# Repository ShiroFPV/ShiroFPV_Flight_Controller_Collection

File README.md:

# ShiroFPV Flight Controller Collection

Open-source FPV flight controller hardware — schematic, PCB layout, symbols and
firmware target, all published in full.

Designed in KiCad, targeted at Betaflight, and licensed so it stays open.

More at **[shirofpv.com/flight-controller](https://shirofpv.com/flight-controller)**

## Boards

| Board | Size | MCU | Analog OSD | Status |
|---|---|---|---|---|
| [**V1** `SFVPF435`](V1_30x30_SFVPF435/) | 30.5 × 30.5 | AT32F435RGT7 | ✅ AT7456 | Released |
| [**V2** `SFVPF435`](V2_20x20_SFVPF435/) | 20.5 × 20.5 | AT32F435CGT7 (48-pin) | ❌ digital only | Released |

---

## V1 — `SFVPF435` (30.5 × 30.5)

| | |
|---|---|
| **MCU** | Artery AT32F435RGT7, up to 288 MHz |
| **Gyro** | ICM-20602 |
| **Baro** | BME280 |
| **OSD** | AT7456 |
| **Blackbox** | 16 Mb onboard flash |
| **USB** | USB-C |
| **Mount** | 30.5 × 30.5 mm standard stack |
| **Firmware** | Betaflight |

### Layout

```
V1_30x30_SFVPF435/
├─ Shematic/          hardware sources — CERN-OHL-S v2
│  ├─ ShiroFPV_Flight_Controller.kicad_sch    schematic
│  ├─ ShiroFPV_Flight_Controller.kicad_pcb    PCB layout
│  ├─ All_Own_Symbols.kicad_sym               custom symbols
│  ├─ All_Own_Symbols.pretty/                 custom footprints
│  └─ .glb                                    3D model
└─ Release/           firmware — GPL-3.0-or-later
   ├─ config.h                                Betaflight target config
   └─ SFPVF435V1.hex                          compiled firmware
```

> Note: `Shematic/` is a typo for `Schematic/` kept as-is so existing links and
> clones don't break.

---

## V2 — `SFVPF435` (20 × 20)

A compact, modern 20.5 × 20.5 mm flight controller designed specifically for lightweight HD-FPV freestyle and racing builds.

| | |
|---|---|
| **MCU** | Artery AT32F435CGT7 (LQFP-48), up to 288 MHz |
| **Gyro** | ICM-42605 (SPI1, 8 kHz sampling) |
| **Baro** | SPL07-003 (I2C1, address `0x76`) |
| **Analog OSD** | **None** — digital video only (HD Zero, DJI O3/O4, Walksnail) |
| **Motors** | 4x DShot motor pads (M1–M4) on TMR5/TMR3 with Bidirectional DShot (RPM filtering) |
| **UARTs** | 5x hardware UARTs (Receiver default on UART5, VTX on UART4) |
| **I2C** | Free I2C1 bus exposed for external compass |
| **USB** | USB-C |
| **Mount** | 20.5 × 20.5 mm M3 / M2 with grommets |
| **Firmware** | Betaflight |

Dropping the legacy analog OSD chip (AT7456E) saves board space, weight, and eliminates video noise on modern digital setups.

### Layout

```
V2_20x20_SFVPF435/
├─ Shematic/          hardware sources — CERN-OHL-S v2
│  ├─ ShiroFPV_Flight_Controller.kicad_sch    schematic
│  ├─ ShiroFPV_Flight_Controller.kicad_pcb    PCB layout
│  ├─ All_Own_Symbols.kicad_sym               custom symbols
│  ├─ All_Own_Symbols.pretty/                 custom footprints
│  └─ .glb                                    3D model
└─ Release/           firmware — GPL-3.0-or-later
   ├─ config.h                                Betaflight target config
   └─ SFPVF435V2.hex                          compiled firmware
```

Details in [`V2_20x20_SFVPF435/`](V2_20x20_SFVPF435/).

---

## Datasheets

Artery's documentation is not redistributed here — it is their copyright.
Download it from the source:

- **AT32F435** — [product page](https://www.arterychip.com/en/product/AT32F435.jsp)
  (datasheet + reference manual)
- **AT32F437** — [product page](https://www.arterychip.com/en/product/AT32F437.jsp)

---

## Building one

The design files are complete — schematic, layout, custom symbols and
footprints. Open `ShiroFPV_Flight_Controller.kicad_pro` in KiCad 8 or newer,
export gerbers, and send them to whichever fab you like.

Flash `SFPVF435V1.hex` or `SFPVF435V2.hex` with the Betaflight Configurator, or build from the
Betaflight sources using `config.h` as the target definition.

It flies. Mostly.

---

## Licence

Two licences, because there are two kinds of work here. Both copyleft.

| Part | Licence |
|---|---|
| Hardware design (`Shematic/`) | [CERN-OHL-S v2](LICENSE) |
| Firmware (`Release/`) | [GPL-3.0-or-later](V1_30x30_SFVPF435/Release/LICENSE) |

**Short version:** use it, modify it, build it, sell it. If you distribute a
modified version, publish your sources under the same licence. You can profit
from this design — you just can't close it.

Full detail and reasoning in **[LICENSING.md](LICENSING.md)**.

---

## Contributing

Issues and pull requests welcome — improvements, fixes, or a revision of your
own. Contributions are accepted under the same licences as above.

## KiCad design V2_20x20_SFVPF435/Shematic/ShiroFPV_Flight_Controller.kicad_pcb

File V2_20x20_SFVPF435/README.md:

# V2 — `SFVPF435` 20 × 20

A compact, high-performance 20.5 × 20.5 mm flight controller powered by the **Artery AT32F435CGT7** (ARM Cortex-M4F @ 288 MHz), designed specifically for lightweight HD-FPV freestyle and racing drones.

## Specifications

| | |
|---|---|
| **MCU** | Artery AT32F435CGT7 (LQFP-48), up to 288 MHz |
| **Gyro** | ICM-42605 via SPI1 (low-noise, up to 8 kHz sampling) |
| **Baro** | SPL07-003 via I2C1 (high-precision altitude sensor) |
| **Analog OSD** | **None** — digital video only (HDZero, Walksnail, DJI O3/O4) |
| **Motors** | 4x DShot motor pads (`PB12`, `PB13`, `PB0`, `PB1`) with Bidirectional DShot (RPM filtering) |
| **UARTs** | 5x hardware UARTs (`UART1`, `UART2`, `UART3`, `UART4`, `UART5` default for CRSF/ELRS) |
| **I2C** | Dedicated I2C1 bus for external compass |
| **Audio/Beeper** | Onboard active-high buzzer driver (N-MOSFET on `PC13`) |
| **LEDs** | Blue (`PB14`) / Green (`PB15`) |
| **ADC** | VBAT (`PA0`, scale 110) & Current sense (`PA1`) |
| **Mount** | 20.5 × 20.5 mm (M3 / M2 with grommets) |
| **Firmware** | Betaflight |

Dropping the legacy analog OSD chip (AT7456E) saves substantial board space and eliminates video noise on modern digital FPV setups.

## Layout

```
V2_20x20_SFVPF435/
├─ Shematic/                                  hardware sources — CERN-OHL-S v2
│  ├─ ShiroFPV_Flight_Controller.kicad_sch    schematic
│  ├─ ShiroFPV_Flight_Controller.kicad_pcb    PCB layout
│  ├─ All_Own_Symbols.kicad_sym               custom symbols
│  ├─ All_Own_Symbols.pretty/                 custom footprints & 3D models
│  └─ .glb                                    3D model
└─ Release/                                   firmware — GPL-3.0-or-later
   ├─ config.h                                Betaflight target config
   └─ SFPVF435V2.hex                          compiled firmware
```

Same two-licence split as V1 — see [LICENSING.md](../LICENSING.md).

## Flashing Betaflight

1. Connect the flight controller via USB.
2. In Betaflight Configurator, open the **Firmware Flasher** tab.
3. Click **Load Firmware [Local]** and select `Release/SFPVF435V2.hex`.
4. Enable **Full chip erase** and click **Flash Firmware**.

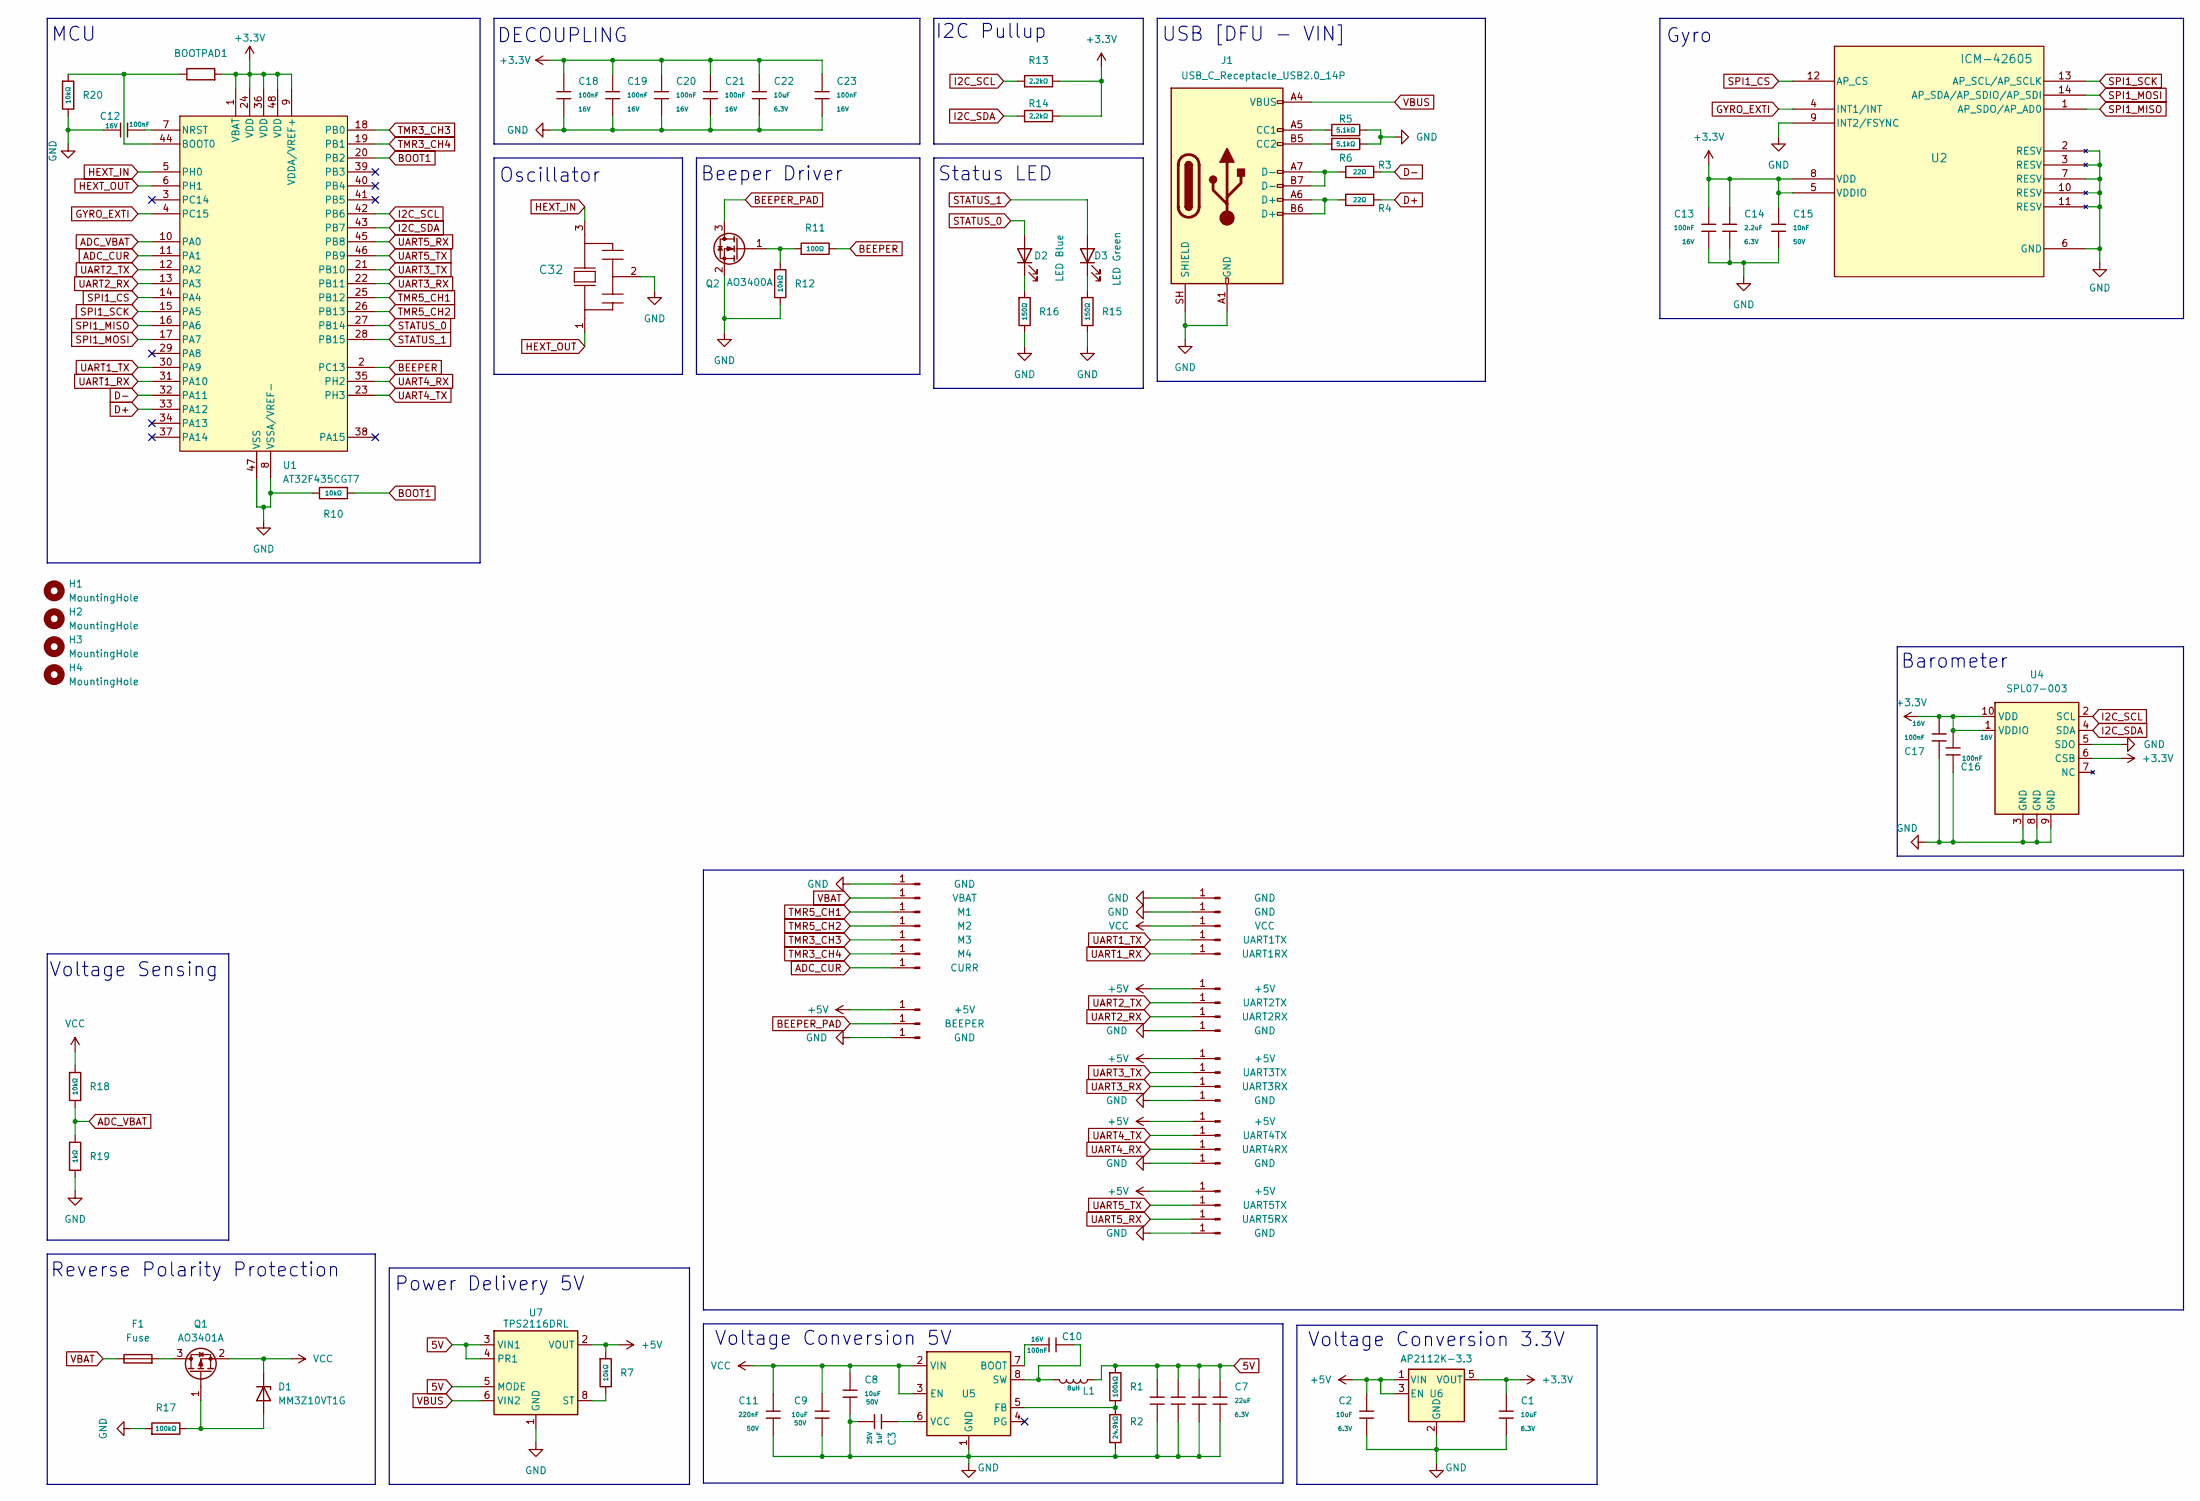
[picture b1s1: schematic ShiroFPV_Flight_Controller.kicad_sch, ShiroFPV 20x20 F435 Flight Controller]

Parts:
BOOTPAD1: SolderJumper-2_P1.3mm_Open_Pad1.0x1.5mm
C1, C2, C22: 10uF; C_0402; Voltage Rated 6.3V; Tolerance ±20%; Part CL05A106MQ5NUNC; LCSC C15525
C3: 1uF; C_0402; Voltage Rated 25V; Tolerance ±10%; Part CL05A105KA5NQNC; LCSC C52923
C4, C5, C6, C7: 22uF; C_0603; Voltage Rated 6.3V; Tolerance ±20%; Part CL10A226MQ8NRNC; LCSC C59461
C8, C9: 10uF; C_0805; Voltage Rated 50V; Tolerance ±10%; Part GRM21BR61H106KE43L; LCSC C440198
C10, C12, C13, C16, C17, C18, C19, C20, C21, C23: 100nF; C_0402; Voltage Rated 16V; Tolerance ±10%; Part CL05B104KO5NNNC; LCSC C1525
C11: 220nF; C_0805; Voltage Rated 50V; Tolerance ±10%; Part CL21B224KBFNNNE; LCSC C5378
C14: 2.2uF; C_0402; Voltage Rated 6.3V; Tolerance ±20%; Part CL05A225MQ5NSNC; LCSC C12530
C15: 10nF; C_0402; Voltage Rated 50V; Tolerance ±10%; Part CL05B103KB5NNNC; LCSC C15195
C32: CSTCE8M00G52-R0; Resonator_SMD_Murata_CSTxExxV-3Pin_3.0x1.1mm; MPN CSTNE8M00G520000R0
D1: MM3Z10VT1G; D_SOD-323_HandSoldering; MPN LM3Z10VT1G
D2: LED Blue; LED_0603_1608Metric
D3: LED Green; LED_0603_1608Metric
F1: Fuse; Fuse_1206_3216Metric
H1, H2, H3, H4: MountingHole; MountingHole_3.2mm_M3
J1: USB_C_Receptacle_USB2.0_14P; USB_C_Receptacle_HRO_TYPE-C-31-M-12
J2, J3, J12, J27, J29, J31, J36, J40: GND; TestPoint_Pad_1.0x1.0mm
J13: VCC; TestPoint_Pad_1.0x1.0mm
J14: UART1TX; TestPoint_Pad_1.0x1.0mm
J15: UART1RX; TestPoint_Pad_1.0x1.0mm
J16: UART2TX; TestPoint_Pad_1.0x1.0mm
J17: UART2RX; TestPoint_Pad_1.0x1.0mm
J18: UART3TX; TestPoint_Pad_1.0x1.0mm
J19: UART3RX; TestPoint_Pad_1.0x1.0mm
J20: UART4TX; TestPoint_Pad_1.0x1.0mm
J21: UART4RX; TestPoint_Pad_1.0x1.0mm
J22: M1; TestPoint_Pad_1.0x1.0mm
J23: M2; TestPoint_Pad_1.0x1.0mm
J24: M3; TestPoint_Pad_1.0x1.0mm
J25: M4; TestPoint_Pad_1.0x1.0mm
J26: CURR; TestPoint_Pad_1.0x1.0mm
J28, J30, J32, J33, J39: +5V; TestPoint_Pad_1.0x1.0mm
J34: UART5TX; TestPoint_Pad_1.0x1.0mm
J35: UART5RX; TestPoint_Pad_1.0x1.0mm
J37: VBAT; TestPoint_Pad_1.0x1.0mm
J38: BEEPER; TestPoint_Pad_1.0x1.0mm
L1: 8uH; L_Wuerth_MAPI-4030
Q1: AO3401A; SOT-23
Q2: AO3400A; SOT-23
R1, R17: 100kΩ; R_0402; Overload Voltage (Max) 50V; Tolerance ±1%; Part 0402WGF1003TCE; LCSC C25741
R2: 24.9kΩ; R_0402
R3, R4: 22Ω; R_0402; Overload Voltage (Max) 50V; Tolerance ±1%; Part 0402WGF220JTCE; LCSC C25092
R5, R6: 5.1kΩ; R_0402; Overload Voltage (Max) 50V; Tolerance ±1%; Part 0402WGF5101TCE; LCSC C25905
R7, R10, R12, R18, R20: 10kΩ; R_0402; Overload Voltage (Max) 50V; Tolerance ±1%; Part 0402WGF1002TCE; LCSC C25744
R11: 100Ω; R_0402; Overload Voltage (Max) 50V; Tolerance ±1%; Part 0402WGF1000TCE; LCSC C25076
R13, R14: 2.2kΩ; R_0402; Overload Voltage (Max) 50V; Tolerance ±1%; Part 0402WGF2201TCE; LCSC C25879
R15, R16: 150Ω; R_0402; Overload Voltage (Max) 50V; Tolerance ±1%; Part 0402WGF1500TCE; LCSC C25082
R19: 1kΩ; R_0402; Overload Voltage (Max) 50V; Tolerance ±1%; Part 0402WGF1001TCE; LCSC C11702
U1: AT32F435CGT7; LQFP-48_7x7mm_P0.5mm; MPN AT32F435CGT7
U2: ICM-42605; LGA-14_3x2.5mm_P0.5mm_LayoutBorder3x4y
U4: SPL07-003; LGA-10_L2.0-W2.0-P0.50-BL; LCSC C3253727
U5: LMR33630ADDA; Texas_HSOP-8-1EP_3.9x4.9mm_P1.27mm_ThermalVias
U6: AP2112K-3.3; SOT-23-5
U7: TPS2116DRL; SOT-583-8

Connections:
5V: C4.1, C5.1, C6.1, C7.1, L1.1, R1.1, U7.3 (VIN1), U7.4 (PR1), U7.5 (MODE)
+3.3V: BOOTPAD1.2, C1.1, C13.1, C14.1, C15.1, C16.2, C17.1, C18.1, C19.1, C20.1, C21.1, C22.1, C23.1, R13.2, R14.2, U1.1 (VBAT), U1.9 (VDDA/VREF+), U1.24 (VDD), U1.36 (VDD), U1.48 (VDD), U2.5 (VDDIO), U2.8 (VDD), U4.1 (VDDIO), U4.6 (CSB), U4.10 (VDD), U6.5 (VOUT)
+5V: C2.1, J28.1 (Pin_1_1), J30.1 (Pin_1_1), J32.1 (Pin_1_1), J33.1 (Pin_1_1), J39.1 (Pin_1_1), R7.1, U6.1 (VIN), U6.3 (EN), U7.2 (VOUT), U7.7 (VOUT)
ADC_CUR: J26.1 (Pin_1_1), U1.11 (PA1)
ADC_VBAT: R18.2, R19.1, U1.10 (PA0)
BEEPER: R11.2, U1.2 (PC13)
BEEPER_PAD: J38.1 (Pin_1_1), Q2.3 (D)
BOOT1: R10.1, U1.20 (PB2)
D+: R4.1, U1.33 (PA12)
D-: R3.2, U1.32 (PA11)
GND: C1.2, C2.2, C3.2, C4.2, C5.2, C6.2, C7.2, C8.2, C9.2, C11.2, C12.2, C13.2, C14.2, C15.2, C16.1, C17.2, C18.2, C19.2, C20.2, C21.2, C22.2, C23.2, C32.2, J1.A1 (GND), J1.A12 (GND), J1.B1 (GND), J1.B12 (GND), J1.SH (SHIELD), J2.1 (Pin_1_1), J3.1 (Pin_1_1), J12.1 (Pin_1_1), J27.1 (Pin_1_1), J29.1 (Pin_1_1), J31.1 (Pin_1_1), J36.1 (Pin_1_1), J40.1 (Pin_1_1), Q2.2 (S), R2.2, R5.2, R6.2, R10.2, R12.2, R15.2, R16.2, R17.1, R19.2, R20.2, U1.8 (VSSA/VREF-), U1.47 (VSS), U2.2 (RESV), U2.3 (RESV), U2.6 (GND), U2.7 (RESV), U2.9 (INT2/FSYNC), U2.10 (RESV), U2.11 (RESV), U4.3 (GND), U4.5 (SDO), U4.8 (GND), U4.9 (GND), U5.1 (GND), U5.9 (GND), U6.2 (GND), U7.1 (GND)
GYRO_EXTI: U1.4 (PC15), U2.4 (INT1/INT)
HEXT_IN: C32.3, U1.5 (PH0)
HEXT_OUT: C32.1, U1.6 (PH1)
I2C_SCL: R13.1, U1.42 (PB6), U4.2 (SCL)
I2C_SDA: R14.1, U1.43 (PB7), U4.4 (SDA)
unnamed: D1.2 (A), Q1.1 (G), R17.2
unnamed: D2.1 (K), R16.1
unnamed: D3.1 (K), R15.1
unnamed: J1.A5 (CC1), R5.1
unnamed: J1.B5 (CC2), R6.1
unnamed: J1.A6 (D+), J1.B6 (D+), R4.2
unnamed: J1.A7 (D-), J1.B7 (D-), R3.1
unnamed: F1.2, Q1.3 (D)
unnamed: Q2.1 (G), R11.1, R12.1
unnamed: BOOTPAD1.1, R20.1, U1.44 (BOOT0)
unnamed: C12.1, U1.7 (NRST)
unnamed: C10.1, U5.7 (BOOT)
unnamed: R1.2, R2.1, U5.5 (FB)
unnamed: C10.2, L1.2, U5.8 (SW)
unnamed: C3.1, U5.6 (VCC)
unnamed: R7.2, U7.8 (ST)
SPI1_CS: U1.14 (PA4), U2.12 (AP_CS)
SPI1_MISO: U1.16 (PA6), U2.1 (AP_SDO/AP_AD0)
SPI1_MOSI: U1.17 (PA7), U2.14 (AP_SDA/AP_SDIO/AP_SDI)
SPI1_SCK: U1.15 (PA5), U2.13 (AP_SCL/AP_SCLK)
STATUS_0: D2.2 (A), U1.27 (PB14)
STATUS_1: D3.2 (A), U1.28 (PB15)
TMR3_CH3: J24.1 (Pin_1_1), U1.18 (PB0)
TMR3_CH4: J25.1 (Pin_1_1), U1.19 (PB1)
TMR5_CH1: J22.1 (Pin_1_1), U1.25 (PB12)
TMR5_CH2: J23.1 (Pin_1_1), U1.26 (PB13)
UART1_RX: J15.1 (Pin_1_1), U1.31 (PA10)
UART1_TX: J14.1 (Pin_1_1), U1.30 (PA9)
UART2_RX: J17.1 (Pin_1_1), U1.13 (PA3)
UART2_TX: J16.1 (Pin_1_1), U1.12 (PA2)
UART3_RX: J19.1 (Pin_1_1), U1.22 (PB11)
UART3_TX: J18.1 (Pin_1_1), U1.21 (PB10)
UART4_RX: J21.1 (Pin_1_1), U1.35 (PH2)
UART4_TX: J20.1 (Pin_1_1), U1.23 (PH3)
UART5_RX: J35.1 (Pin_1_1), U1.45 (PB8)
UART5_TX: J34.1 (Pin_1_1), U1.46 (PB9)
VBAT: F1.1, J37.1 (Pin_1_1)
VBUS: J1.A4 (VBUS), J1.A9 (VBUS), J1.B4 (VBUS), J1.B9 (VBUS), U7.6 (VIN2)
VCC: C8.1, C9.1, C11.1, D1.1 (K), J13.1 (Pin_1_1), Q1.2 (S), R18.1, U5.2 (VIN), U5.3 (EN)

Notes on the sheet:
Voltage Sensing
USB [DFU - VIN]
Status LED
DECOUPLING
Barometer
I2C Pullup
Voltage Conversion 5V
Oscillator
Power Delivery 5V
Beeper Driver
MCU
Reverse Polarity Protection
Gyro
Voltage Conversion 3.3V

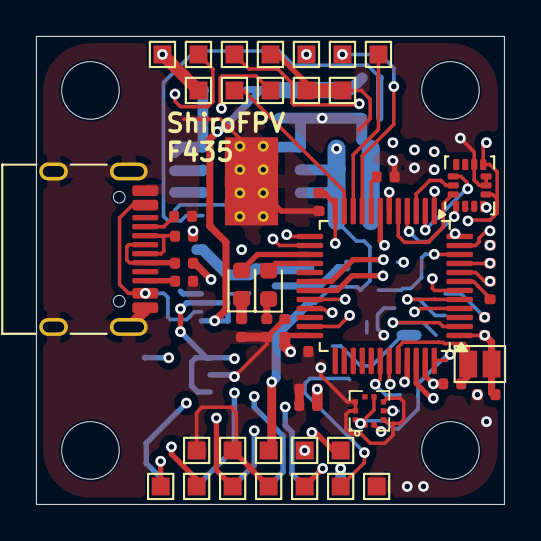
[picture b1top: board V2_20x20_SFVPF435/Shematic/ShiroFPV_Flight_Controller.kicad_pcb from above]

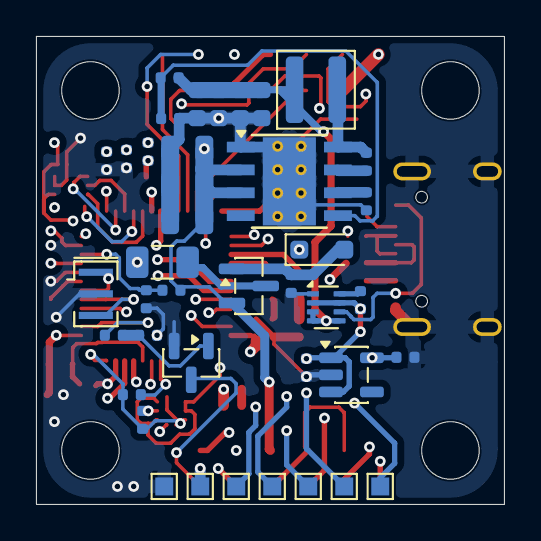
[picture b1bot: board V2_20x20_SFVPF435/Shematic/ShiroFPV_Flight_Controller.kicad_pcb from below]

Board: 4 copper layers, 26.0 x 26.0 mm, 92 parts (40 on the bottom side), 55 nets.

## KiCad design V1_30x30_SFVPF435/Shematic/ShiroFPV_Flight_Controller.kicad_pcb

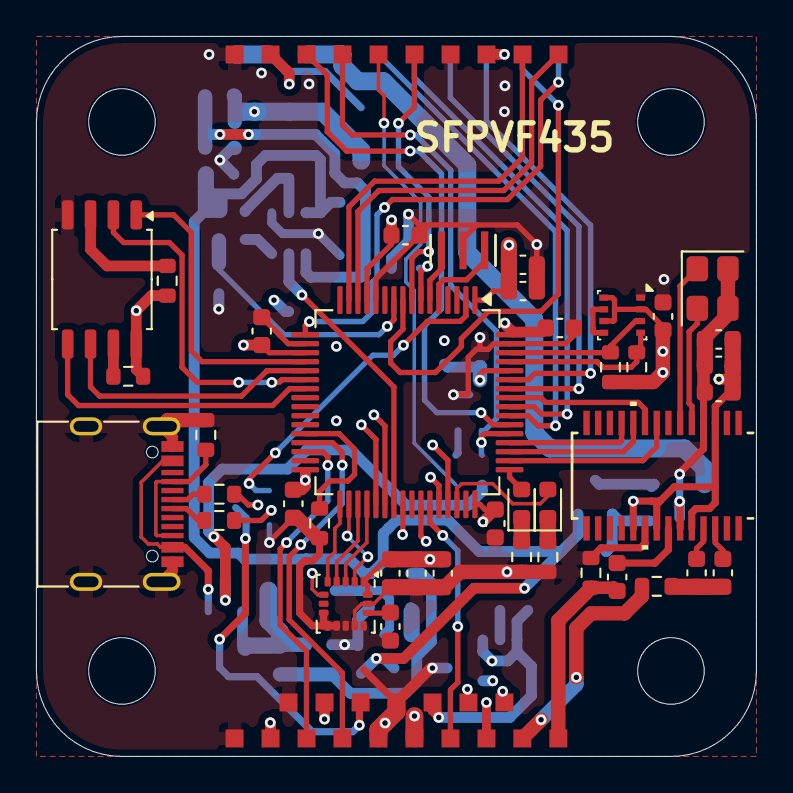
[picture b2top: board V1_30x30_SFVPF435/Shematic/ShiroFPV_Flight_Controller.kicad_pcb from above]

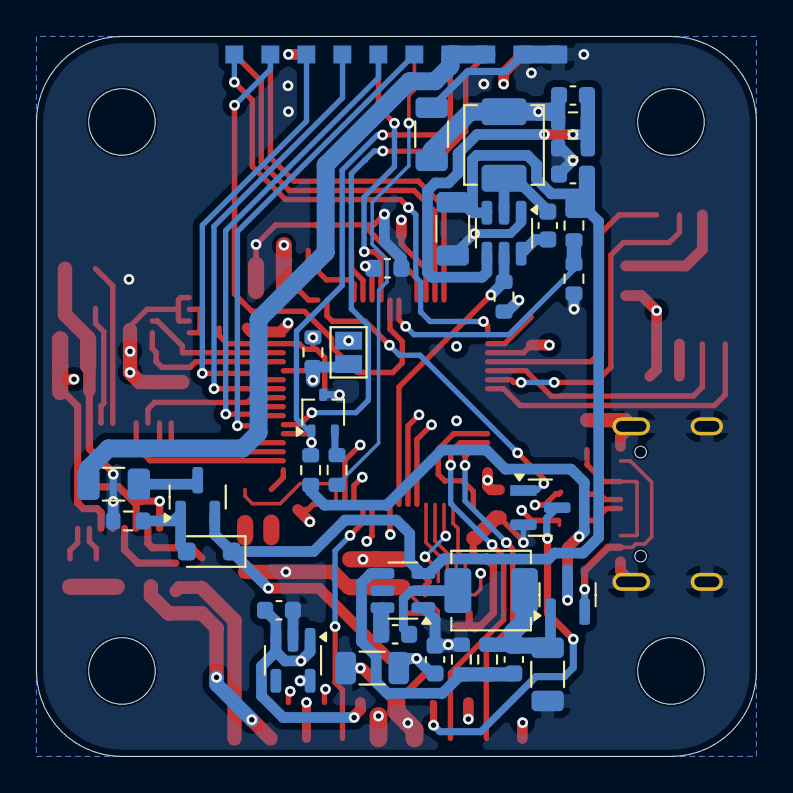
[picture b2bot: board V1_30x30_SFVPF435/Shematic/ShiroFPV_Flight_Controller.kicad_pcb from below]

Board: 4 copper layers, 40.0 x 40.0 mm, 112 parts (45 on the bottom side), 79 nets.

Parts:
C1, C2, C4, C6, C7, C10, C11, C12, C13, C15, C16, C20, C23, C25, C26, C27, C28, C29: 100nF; C_0603_1608Metric
C3: 10nF; C_0603_1608Metric
C5, C31: 1uF; C_0603_1608Metric
C8, C9: 47uF; C_0603_1608Metric
C14, C38: 10uF; C_1206_3216Metric
C17: 100pF; C_0603_1608Metric
C18, C19: 47uF; C_1206_3216Metric
C22: 150pF; C_0603_1608Metric
C32: CSTCE8M00G52-R0; 8MHz-Osciallator.kicad_sym
C39: 2.2uF; C_0603_1608Metric
D1: MM3Z10VT1G; D_SOD-323_HandSoldering
D2: LED Blue; LED_0603_1608Metric
D3: LED Yellow; LED_0603_1608Metric
D4: PMEG4005CT,215; SOT-23
F1: Fuse; Fuse_1206_3216Metric
J1, J2, J46: GND; TestPoint_Pad_1.0x1.0mm_No_Silkscreen
J3, J4: VBAT; TestPoint_Pad_1.0x1.0mm_No_Silkscreen
J5: M1; TestPoint_Pad_1.0x1.0mm_No_Silkscreen
J6: M2; TestPoint_Pad_1.0x1.0mm_No_Silkscreen
J7: M3; TestPoint_Pad_1.0x1.0mm_No_Silkscreen
J8: M4; TestPoint_Pad_1.0x1.0mm_No_Silkscreen
J9: CUR; TestPoint_Pad_1.0x1.0mm_No_Silkscreen
J10: TLM; TestPoint_Pad_1.0x1.0mm_No_Silkscreen
J11: Video_Out; TestPoint_Pad_1.0x1.0mm_No_Silkscreen
J12: Video_IN; TestPoint_Pad_1.0x1.0mm_No_Silkscreen
J13: 5V3; TestPoint_Pad_1.0x1.0mm_No_Silkscreen
J14: RX3; TestPoint_Pad_1.0x1.0mm_No_Silkscreen
J15: TX3; TestPoint_Pad_1.0x1.0mm_No_Silkscreen
J16: GND3; TestPoint_Pad_1.0x1.0mm_No_Silkscreen
J17: 5V4; TestPoint_Pad_1.0x1.0mm_No_Silkscreen
J18: RX4; TestPoint_Pad_1.0x1.0mm_No_Silkscreen
J19: TX4; TestPoint_Pad_1.0x1.0mm_No_Silkscreen
J20: GND4; TestPoint_Pad_1.0x1.0mm_No_Silkscreen
J24: +5V; TestPoint_Pad_1.0x1.0mm_No_Silkscreen
J25: RSSI; TestPoint_Pad_1.0x1.0mm_No_Silkscreen
J26: GND5; TestPoint_Pad_1.0x1.0mm_No_Silkscreen
J29: SBUS; TestPoint_Pad_1.0x1.0mm_No_Silkscreen
J30: 5V5; TestPoint_Pad_1.0x1.0mm_No_Silkscreen
J31: RX5; TestPoint_Pad_1.0x1.0mm_No_Silkscreen
J32: TX5; TestPoint_Pad_1.0x1.0mm_No_Silkscreen
J33: RX6; TestPoint_Pad_1.0x1.0mm_No_Silkscreen
J34: 5V6; TestPoint_Pad_1.0x1.0mm_No_Silkscreen
J35: GND6; TestPoint_Pad_1.0x1.0mm_No_Silkscreen
J36: TX6; TestPoint_Pad_1.0x1.0mm_No_Silkscreen
J37: 10V; TestPoint_Pad_1.0x1.0mm_No_Silkscreen
J38: RX1; TestPoint_Pad_1.0x1.0mm_No_Silkscreen
J39: TX1; TestPoint_Pad_1.0x1.0mm_No_Silkscreen
J40: GND1; TestPoint_Pad_1.0x1.0mm_No_Silkscreen
J42: B-; TestPoint_Pad_1.0x1.0mm_No_Silkscreen
JP1: SolderJumper_2_Open; SolderJumper-2_P1.3mm_Open_Pad1.0x1.5mm
L1: 10uH; L_APV_APH0412
L2: 15uH; L_APV_APH0412
P1: USB_C_Plug_USB2.0; USB_C_Receptacle_G-Switch_GT-USB-7010ASV
Q1: AO3401A; SOT-23
Q2: AO3400A; SOT-23
Q3: BC817W; SOT-323_SC-70
R1, R7, R11: 100K; R_0603_1608Metric
R2: 12.3K; R_0603_1608Metric
R3, R4: 75R; R_0603_1608Metric
R5, R6, R9, R10, R19, R20: 10K; R_0603_1608Metric
R8: 6.2K; R_0603_1608Metric
R12, R13: 22R; R_0603_1608Metric
R14: 5.1K; R_0603_1608Metric
R15, R16: 150R; R_0603_1608Metric
R17, R29: 2.2K; R_0603_1608Metric
R21: 2K; R_0603_1608Metric
R22: 4.7K; R_0603_1608Metric
R27: 18K; R_0603_1608Metric
U1: AT32F435RGT7; LQFP-64_10x10mm_P0.5mm
U3: ICM-20602; LGA-16_3x3mm_P0.5mm_LayoutBorder3x5y
U4: BME280; Bosch_LGA-8_2.5x2.5mm_P0.65mm_ClockwisePinNumbering
U5: TPS54302; SOT-23-6
U6: TPS54302DDCR; SOT-23-6
U7: RT9013-33GB; SOT-23-5
U8: W25Q128JVS; SOIC-8_5.3x5.3mm_P1.27mm
U10: AT7456
Y2: 27MHz; Crystal_SMD_3225-4Pin_3.2x2.5mm

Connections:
9V_Enable: R9.2, U1.39 (PC8), U6.5 (EN)
+3.3V: C3.1, C6.2, C10.1, C23.1, C25.1, C26.1, C27.1, C28.1, C29.1, C31.1, C39.1, JP1.1 (A), R9.1, R17.1, R19.1, R20.2, R29.1, U1.1 (VBAT), U1.13 (VDDA), U1.19 (VDD), U1.32 (VDD), U1.48 (VDD), U1.64 (VDD), U3.1 (VDDIO), U3.16 (VDD), U4.2 (CSB), U4.6 (VDDIO), U4.8 (VDD), U7.5 (VOUT), U8.8 (VCC)
+5V: C5.1, C7.2, C12.2, C13.1, D4.3, J13.1 (Pin_1_1), J17.1 (Pin_1_1), J24.1 (Pin_1_1), J30.1 (Pin_1_1), J34.1 (Pin_1_1), R10.1, U7.1 (VIN), U7.3 (ON/~OFF), U10.3 (DVDD), U10.19 (*RESET), U10.21 (AVDD), U10.24 (PVDD)
+5V_BEC: C17.1, C18.1, D4.1, L1.2, R1.1
+10V: C19.1, C22.1, J37.1 (Pin_1_1), L2.2, R7.1
ADC_CURRENT: J9.1 (Pin_1_1), U1.9 (PC1)
ADC_RSSI: J25.1 (Pin_1_1), U1.8 (PC0)
ADC_VBAT: R21.1, R27.2, U1.10 (PC2)
BEEPER: Q2.2 (G), U1.2 (PC13)
BEEPER_B-: J42.1 (Pin_1_1), Q2.1 (D)
BOOT0: JP1.2 (B), R5.1, U1.60 (BOOT0)
BOOT1: R6.1, U1.28 (PB2)
FLASH_CS: U1.20 (PA4), U8.1 (~CS)
FLASH_MISO: U1.22 (PA6), U8.2 (DO/IO_{1})
FLASH_MOSI: U1.23 (PA7), U8.5 (DI/IO_{0})
FLASH_SCK: U1.21 (PA5), U8.6 (CLK)
GND: C1.1, C3.2, C4.1, C5.2, C6.1, C7.1, C10.2, C12.1, C13.2, C14.2, C15.2, C18.2, C19.2, C20.2, C23.2, C25.2, C26.2, C27.2, C28.2, C29.2, C31.2, C32.2, C38.2, C39.2, J1.1 (Pin_1_1), J2.1 (Pin_1_1), J16.1 (Pin_1_1), J20.1 (Pin_1_1), J26.1 (Pin_1_1), J35.1 (Pin_1_1), J40.1 (Pin_1_1), J46.1 (Pin_1_1), P1.A1 (GND), P1.A12 (GND), P1.B1 (GND), P1.B12 (GND), P1.S1 (SHIELD), Q2.3 (S), Q3.3 (E), R2.1, R4.2, R5.2, R6.2, R8.2, R11.2, R14.1, R15.2, R16.2, R21.2, U1.12 (VSSA), U1.18 (VSS), U1.63 (VSS), U3.8 (FSYNC), U3.9 (GND), U3.10 (GND), U3.11 (GND), U3.12 (GND), U3.13 (GND), U3.15 (GND), U4.1 (GND), U4.5 (SDO), U4.7 (GND), U5.1 (GND), U6.1 (GND), U7.2 (GND), U8.4 (GND), U10.4 (DGND), U10.20 (AGND), U10.23 (PGND), Y2.3, Y2.4
GYRO_CS: U1.33 (PB12), U3.5 (~CS)
GYRO_INIT: U1.40 (PC9), U3.6 (INT)
GYRO_SCK: U1.34 (PB13), U3.2 (SCL/SPC)
GYRO_SDA: U1.36 (PB15), U3.3 (SDA/SDI)
GYRO_SDO: U1.35 (PB14), U3.4 (SAO/SD0)
I2C_SCL: R17.2, U1.61 (PB8), U4.4 (SCK)
I2C_SDA: R29.2, U1.62 (PB9), U4.3 (SDI)
LEDSTATUS0: D2.2 (A), U1.49 (PA14)
LEDSTATUS1: D3.2 (A), U1.46 (PA13)
M1: J5.1 (Pin_1_1), U1.55 (PB3)
M2: J6.1 (Pin_1_1), U1.56 (PB4)
M3: J7.1 (Pin_1_1), U1.58 (PB6)
M4: J8.1 (Pin_1_1), U1.59 (PB7)
unnamed: C8.2, C9.2, R3.1
unnamed: D1.2 (A), Q1.2 (G), R11.1
unnamed: D2.1 (K), R16.1
unnamed: D3.1 (K), R15.1
unnamed: P1.A5 (CC), P1.B5 (VCONN), R14.2
unnamed: P1.A6 (D+), R12.1
unnamed: P1.A7 (D-), R13.1
unnamed: F1.2, Q1.1 (D)
unnamed: Q3.2 (B), R22.2
unnamed: C4.2, U1.7 (NRST)
unnamed: C1.2, U3.14 (REGOUT)
unnamed: C2.2, U5.6 (BOOT)
unnamed: C17.2, R1.2, R2.2, U5.4 (FB)
unnamed: C2.1, L1.1, U5.2 (SW)
unnamed: C16.2, U6.6 (BOOT)
unnamed: C22.2, R7.2, R8.1, U6.4 (FB)
unnamed: C16.1, L2.1, U6.2 (SW)
unnamed: R20.1, U8.7 (~HOLD/~RESET/IO_{3})
unnamed: R19.2, U8.3 (~WP/IO_{2})
unnamed: U10.5 (CLKIN), Y2.2
unnamed: C9.1, U10.25 (SAG)
unnamed: C11.1, U10.22 (VIN)
unnamed: C8.1, U10.26 (VOUT)
unnamed: U10.6 (XFB), Y2.1
OSC_IN: C32.3, U1.5 (PH0)
OSC_OUT: C32.1, U1.6 (PH1)
OSD_CS: U1.50 (PA15), U10.8 (*CS)
OSD_MISO: U1.52 (PC11), U10.11 (SDOUT)
OSD_MOSI: U1.57 (PB5), U10.9 (SDIN)
OSD_SCK: U1.51 (PC10), U10.10 (SCLK)
SBUS: J29.1 (Pin_1_1), R22.1
UART1RX: J38.1 (Pin_1_1), U1.43 (PA10)
UART1TX: J39.1 (Pin_1_1), U1.42 (PA9)
UART2RX: J10.1 (Pin_1_1), U1.17 (PA3)
UART3RX: J14.1 (Pin_1_1), U1.30 (PB11)
UART3TX: J15.1 (Pin_1_1), U1.29 (PB10)
UART4RX: J18.1 (Pin_1_1), U1.15 (PA1)
UART4TX: J19.1 (Pin_1_1), U1.14 (PA0)
UART5RX: J31.1 (Pin_1_1), U1.54 (PD2)
UART5TX: J32.1 (Pin_1_1), Q3.1 (C), R10.2, U1.53 (PC12)
UART6RX: J33.1 (Pin_1_1), U1.38 (PC7)
UART6TX: J36.1 (Pin_1_1), U1.37 (PC6)
USBD+: R12.2, U1.45 (PA12)
USBD-: R13.2, U1.44 (PA11)
VBAT: F1.1, J3.1 (Pin_1_1), J4.1 (Pin_1_1)
VBUS: D4.2, P1.A4 (VBUS), P1.A9 (VBUS), P1.B4 (VBUS), P1.B9 (VBUS)
VIN: C14.1, C15.1, C20.1, C38.1, D1.1 (K), Q1.3 (S), R27.1, U5.3 (VIN), U6.3 (VIN)
V_IN: C11.2, J12.1 (Pin_1_1), R4.1
V_OUT: J11.1 (Pin_1_1), R3.2

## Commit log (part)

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2026-05-19 V1(2)
2026-05-19 V1(3)
2026-06-26 Add KiCad project files and 3D model
    Add initial project artifacts for V1_30x30_SFVPF435: include a .glb 3D model, a .kicad_prl project preferences file, and KiCad lock files. Also add macOS .DS_Store files. Tweak the board file (ShiroF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
